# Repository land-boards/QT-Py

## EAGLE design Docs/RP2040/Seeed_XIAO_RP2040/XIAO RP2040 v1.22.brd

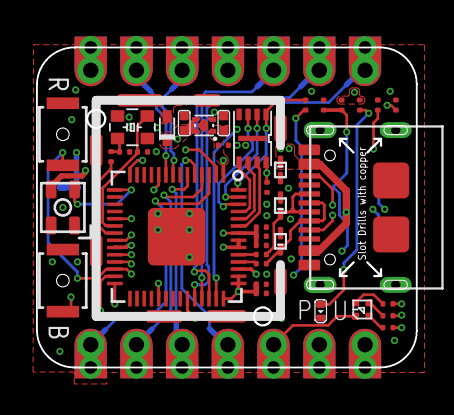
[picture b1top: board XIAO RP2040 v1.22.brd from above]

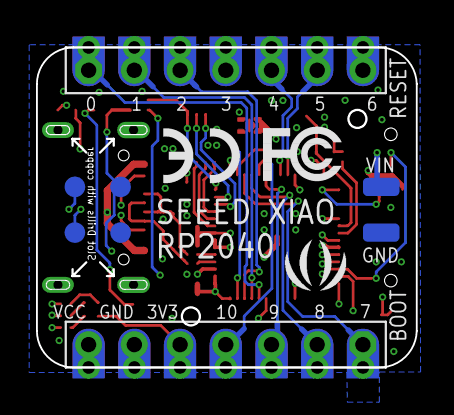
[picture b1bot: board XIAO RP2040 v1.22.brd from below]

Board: 4 copper layers, 21.1 x 17.8 mm, 47 parts (7 on the bottom side), 44 nets.

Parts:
BOOT: BUTTON_TD1183SA
C2, C3, C7, C10, C15, C18, C21: 100nF; 0201_NORMAL\NOSILK
C5, C6: 10uF; C0402
C16: 1uF; 0201_NORMAL\NOSILK
C19, C20: 12pF; 0201_NORMAL\NOSILK
D1, D8, D9: DF2S6.8FS; SOD-923
D2: NRS0320MW2T1G; SOD523
GND: TP-80X40MIL
J1: SHIELDING-COVER_XIAO_RP2040_PRD
J2, J4: DNP; H7-HALF-HOLE-2.54
LOGO_SEEED: SEEED-SILK--TNAME-160*153MIL
PWR: RED; LED-0402
R1, R2: 5.1k; R0201
R3: 2.2K; R0201
R4: 4.7K; R0201
R5: 10k; R0201
R6, R14, R24: 1k; R0201
R7: 11K; R0201
R22, R23: 27R; R0201
RESET: BUTTON_TD1183SA
RGB1: LED_RGB_4P; LED_RGB_2427
RGB2: 1010-4P
TP1, TP3, TP5, TP6: TP-D45MIL
U3: GD25Q16CEIG_USON8_3X2MM
U4: LDO_DFN11_4P; LDO_DFN1*1_4P
U6: RP2040_QFN56
USB1: USB2.0-TYPE-C
VIN: TP-80X40MIL
X3: CRYSTAL_4P_2520

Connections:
1V1: C15.1, C16.1, C18.1, U6.23, U6.45, U6.50
3V3: C3.1, C6.2, C7.1, C10.1, C21.2, J4.5, J4.17, R5.1, R6.1, RGB2.+, U3.8, U4.1, U6.1, U6.10, U6.22, U6.33, U6.42, U6.43, U6.44, U6.48, U6.49
A0: J2.1, J2.13, U6.38
A1: J2.2, J2.14, U6.39
A2: J2.3, J2.15, U6.40
A3: J2.4, J2.16, U6.41
GND: BOOT.2, C2.2, C3.2, C5.1, C6.1, C7.2, C10.2, C15.2, C16.2, C18.2, C19.1, C20.2, C21.1, D1.2, D8.2, D9.2, GND.1, J1.1, J1.2, J1.3, J1.4, J1.5, J1.6, J1.7, J1.8, J4.6, J4.18, PWR.-, R1.2, R2.1, RESET.2, RGB1.2, TP6.T, U3.4, U3.9, U4.2, U4.5, U6.19, U6.57, USB1.A1_B12, USB1.B1_A12, USB1.S1, USB1.S2, USB1.S3, USB1.S4, USB1.S5, USB1.S6, X3.2, X3.4
IO16_RGB-G: R7.2, U6.27
IO17_RGB-R: R4.2, U6.28
IO25_RGB-B: R3.2, U6.37
MISO: J4.3, J4.15, U6.6
MOSI: J4.4, J4.16, U6.5
unnamed: R1.1, USB1.A5
unnamed: R2.2, USB1.B5
unnamed: R3.1, RGB2.B-
unnamed: R7.1, RGB2.G-
unnamed: R4.1, RGB2.R-
unnamed: C20.1, R24.1, X3.3
unnamed: PWR.+, R6.2
NEOPIX: RGB1.3, U6.15
NEO_PWR: RGB1.4, U6.14
QSPI_CSN: R14.2, U3.1, U6.56
QSPI_SCK: U3.6, U6.52
QSPI_SIO_0: U3.5, U6.53
QSPI_SIO_1: U3.2, U6.55
QSPI_SIO_2: U3.3, U6.54
QSPI_SIO_3: U3.7, U6.51
RP2040_BOOT: BOOT.1, R14.1
RUN: C2.1, R5.2, RESET.1, TP1.T, U6.26
RX: J4.1, J4.13, U6.3
SCK: J4.2, J4.14, U6.4
SCL: J2.6, J2.18, U6.9
SDA: J2.5, J2.17, U6.8
SWDCLK: TP3.T, U6.24
SWDIO: TP5.T, U6.25
TX: J2.7, J2.19, U6.2
USB_D+: D8.1, R23.2, USB1.A6, USB1.B6
USB_D-: D9.1, R22.2, USB1.A7, USB1.B7
USB_DM: R22.1, U6.46
USB_DP: R23.1, U6.47
VBUS: D1.1, D2.A, J4.7, J4.19, USB1.A4_B9, USB1.B4_A9
VIN: C5.2, D2.C, U4.3, U4.4, VIN.1
XIN: C19.2, U6.20, X3.1
XOUT: R24.2, U6.21

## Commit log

2022-06-06 Initial code check-in
2022-06-06 Organize code in folders
2022-06-10 QT Py and XIAO docs
2022-06-11 QT Py and XIAO code and docs
2022-06-11 CircuitPython code
2022-06-11 Shuffle folders
2022-06-11 CircuitPython libraries
2022-06-11 Tested/working code
2022-06-12 More CircuitPython code
2022-06-13 MyMenu code working
2022-06-13 Loader V2 file selection works
2022-06-13 Working file selector, top level menu
2022-06-14 XIAO SMAD21 CircuitPython code
2022-06-24 examples
2022-06-26 Docs
2022-06-26 Add status LED
2022-06-26 blink led, solid = sync
2022-06-26 LED optimized
2022-06-26 Working nicely with LED blinking while syncing
2022-07-11 MMBASIC port to QT Py
2022-07-13 QTPy49 SD Card
2022-07-13 Library tweeks
2022-07-13 Tweeks
2022-07-13 QTPy card driver
2022-07-13 4x I2CIO-8 cards
2022-07-20 Added RS-232 Serial
2022-07-21 MMBASIC programs
2022-07-21 Shuffle around programs, update readme docs
2022-07-21 Shuffle around stuff
2022-07-24 Build pics
2022-08-16 PS2 Keyboard to Serial
2022-10-20 Test code
2022-10-20 Working MIDI to CV
    USB version is working
2022-10-20 MOVE SYNTH FILES
2022-10-24 MIDI to CV code
2022-10-24 Random pitch/mod generator
2022-10-25 Made note rate pot log so it has a better range feel
2022-10-25 Improve pot response times
2022-11-11 Improve GATE control
2022-11-11 Improve gate Handling
2022-11-28 midi friends
2023-01-16 ER-USB-MIDI
